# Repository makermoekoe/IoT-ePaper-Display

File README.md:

# IoT ePaper Display

The IoT ePaper Display should be able to show different messages from smart home devices or temperature measurements. The main part is the 2,9" ePaper Display, which fits directly onto the self designed PCB. The PCB contains an ESP8266, a linear voltage regulator, a LiPo charger circuit and a temperature sensor on the bottom of the board. Furthermore it offers an optional I2C jack to connect some other sensors or devices.

It will use the deep sleep functionality of the microcontroller to reduce power consumption and to elongate battery lifetime.

I just have started this project so it is currently a work in progress and will be updated frequently.

## Requirements

- PCB
- 2.9" ePaper Display
- ESP8266-12F
- MCP1700 3.3V LDO
- MCP9808 temperature sensor
- MCP73831 LiPo charger
- SMD power switch
- micro usb jack
- 2x 3x6mm SMD button
- JST-PH-2 2mm 90° SMD connector
- JST-PH-4 2mm 90° SMD connector
- LiPo battery

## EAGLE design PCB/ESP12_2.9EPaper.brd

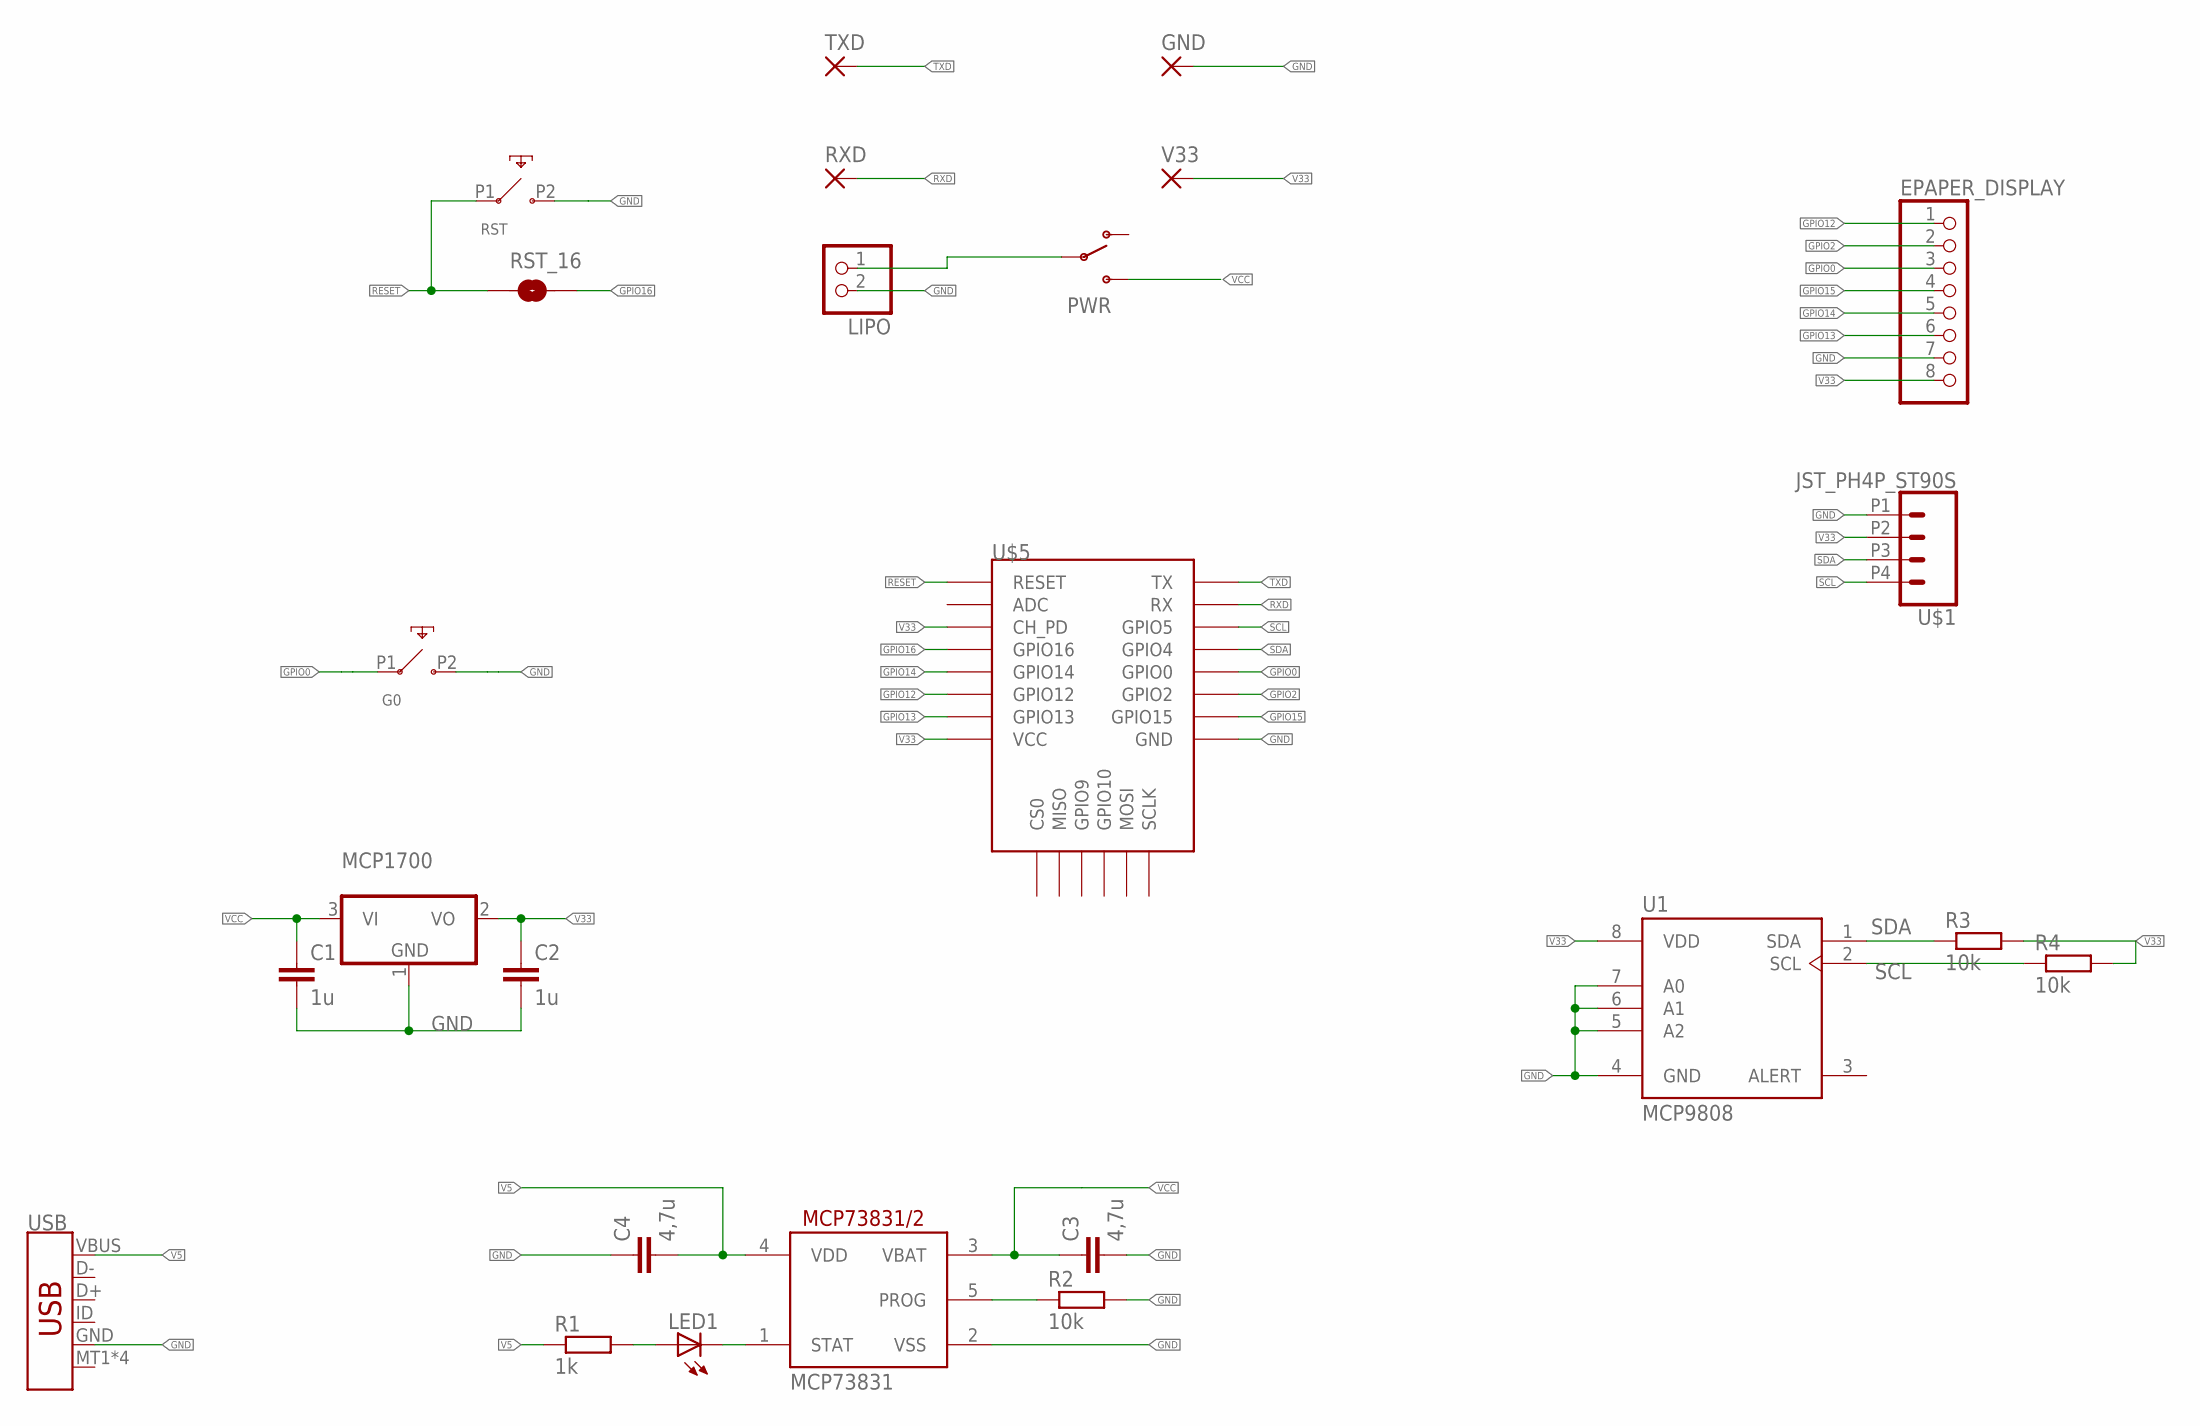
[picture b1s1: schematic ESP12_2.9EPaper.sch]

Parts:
C1, C2: 1u; C1206
C3, C4: 4,7u; C1206
EPAPER_DISPLAY: PINHD-1X8; 1X08
G0: 6X3_SMD_BUTTON_HALF; 6X3BUTTON
GND: WIREPADSMD1,27-254; SMD1,27-2,54
LED1: LEDCHIPLED_1206; CHIPLED_1206
LIPO: JST_2PIN-SMT-RA; JST-PH-2-SMT-RA
MCP1700: MCP1703CB; SOT23
MCP73831: MCP73831/OT; SOT23-5L
PWR: SWITCH_SPDT; KPS-1290
R1: 1k; M1206
R2, R3, R4: 10k; M1206
RST: 6X3_SMD_BUTTON_HALF; 6X3BUTTON
RST_16: JUMPER-SMT_2_NO_NO-SILK; SMT-JUMPER_2_NO_NO-SILK
RXD: WIREPADSMD1,27-254; SMD1,27-2,54
TXD: WIREPADSMD1,27-254; SMD1,27-2,54
U1: MCP9808; MSOP-8
U$1: JST_PH4P_ST90S
U$5: ESP8266-12F-SMD; ESP8266-12F
USB: USB_MICRO-B_SMT; USB-MICROB
V33: WIREPADSMD1,27-254; SMD1,27-2,54

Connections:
GND: C1.2, C2.2, C3.2, C4.1, EPAPER_DISPLAY.7, G0.P2, GND.1, LIPO.2 (1), MCP1700.1 (GND), MCP73831.2 (VSS), R2.2, RST.P2, U1.4 (GND), U1.5 (A2), U1.6 (A1), U1.7 (A0), U$1.P1 (1), U$5.GND, USB.GND
GPIO0: EPAPER_DISPLAY.3, G0.P1, U$5.GPIO0
GPIO2: EPAPER_DISPLAY.2, U$5.GPIO2
GPIO12: EPAPER_DISPLAY.1, U$5.GPIO12
GPIO13: EPAPER_DISPLAY.6, U$5.GPIO13
GPIO14: EPAPER_DISPLAY.5, U$5.GPIO14
GPIO15: EPAPER_DISPLAY.4, U$5.GPIO15
GPIO16: RST_16.2, U$5.GPIO16
unnamed: LIPO.1 (2), PWR.P
unnamed: MCP73831.5 (PROG), R2.1
unnamed: LED1.C, MCP73831.1 (STAT)
unnamed: LED1.A, R1.2
RESET: RST.P1, RST_16.1, U$5.RESET
RXD: RXD.1, U$5.RXD (RX)
SCL: R4.1, U1.2 (SCL), U$1.P4 (4), U$5.GPIO5
SDA: R3.1, U1.1 (SDA), U$1.P3 (3), U$5.GPIO4
TXD: TXD.1, U$5.TXD (TX)
V5: C4.2, MCP73831.4 (VDD), R1.1, USB.VBUS
V33: C2.1, EPAPER_DISPLAY.8, MCP1700.2 (VO), R3.2, R4.2, U1.8 (VDD), U$1.P2 (2), U$5.EN (CH_PD), U$5.VCC, V33.1
VCC: C1.1, C3.1, MCP1700.3 (VI), MCP73831.3 (VBAT), PWR.S

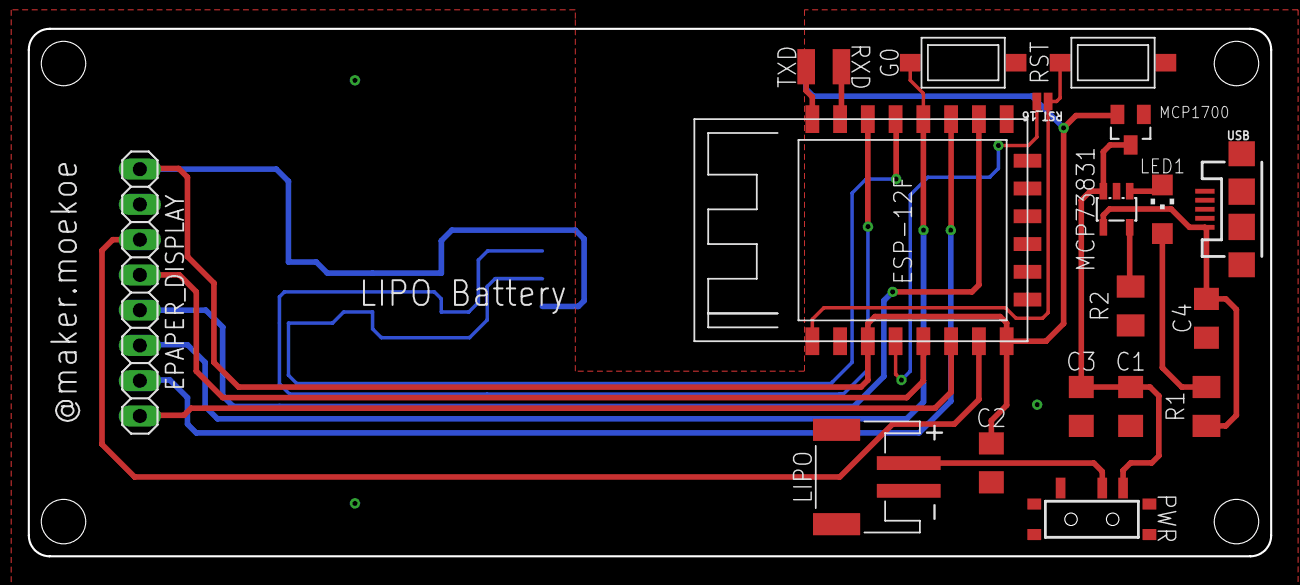
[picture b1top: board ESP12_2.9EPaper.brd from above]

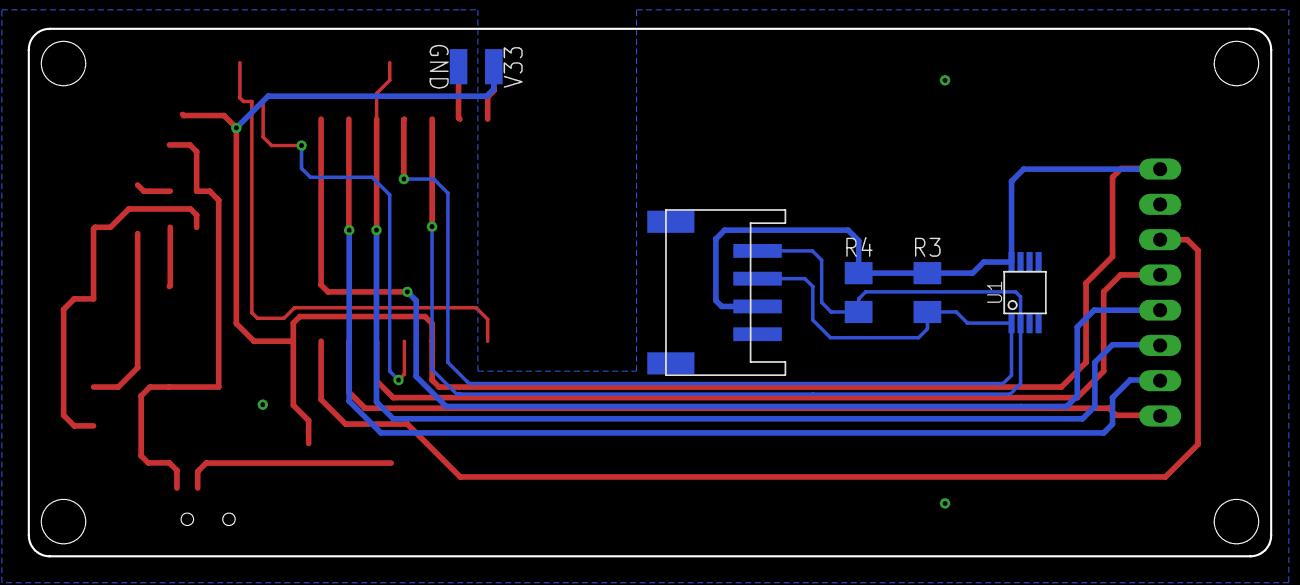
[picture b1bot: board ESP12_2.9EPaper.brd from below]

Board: 2 copper layers, 89.5 x 38.0 mm, 25 parts (6 on the bottom side), 20 nets.

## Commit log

2018-12-05 eagle files

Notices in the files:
parts and their libraries:
SparkFun-Jumpers: Licensing: Creative Commons ShareAlike 4.0 International - https://creativecommons.org/licenses/by-sa/4.0
